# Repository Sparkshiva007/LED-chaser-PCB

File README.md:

# LED Chaser Circuit (555 Timer + CD4017) – KiCad Project

A classic LED chaser circuit designed using **KiCad**, powered by a 555 timer and CD4017 decade counter IC. It lights up a series of LEDs one-by-one in sequence, creating a "running light" or "Knight Rider" effect.

---

## 🎯 What This Project Does

- Generates a continuous sequence of LED flashes (like chasing lights)
- Uses simple and easily available ICs: 555 Timer & CD4017
- Adjustable speed using a timing resistor/capacitor combo
- Designed as a **KiCad project** with proper PCB layout and schematic
- Great for learning KiCad, PCB design, or digital electronics

---

## 📦 Features

- 10 output LEDs (can be reduced as needed)
- 555 Timer in **astable mode** for clock generation
- CD4017 Decade Counter to handle sequencing
- Clean PCB layout with labeled connectors and components
- Optional trimmer resistor to control LED chasing speed

---

## 🧰 Components Used

| Component        | Quantity |
|------------------|----------|
| 555 Timer IC     | 1        |
| CD4017 IC        | 1        |
| LEDs             | 10       |
| 1kΩ Resistors    | 10       |
| 10kΩ potentiometer   | 1        |
| 100nF Capacitor  | 1        |
| 10µF Capacitor   | 1        |
| Power Source (5V–9V) | 1    |

---

## 🚀 How to Use

1. **Open the project** in KiCad 7.x or newer.
2. View/edit the schematic in the `.kicad_sch` file.
3. Open the `.kicad_pcb` file to view or modify the PCB layout.
4. Export Gerber files if you want to fabricate the board.
5. Assemble the board using through-hole components.
6. Power it up and enjoy the chasing LED effect!

## 🔧 Tuning the Speed

You can control how fast the LEDs chase using the **10k potentiometer** connected to the 555 timer. The values used are:

---

## 💡 Educational Value

This is a beginner-friendly project that introduces:
- Basic timer circuits
- Counter IC operation
- Sequential logic
- KiCad schematic and PCB design

Perfect for hobbyists, students, or anyone getting started with PCB design!

---

## Credits

Circuit concept inspired by the classic LED chaser project found in many electronics books. This version was fully re-created in KiCad by **Shiva Projects** for educational use.

---

## 📄 License

Open-source hardware. You are free to modify, improve, or manufacture the board for personal or educational use.

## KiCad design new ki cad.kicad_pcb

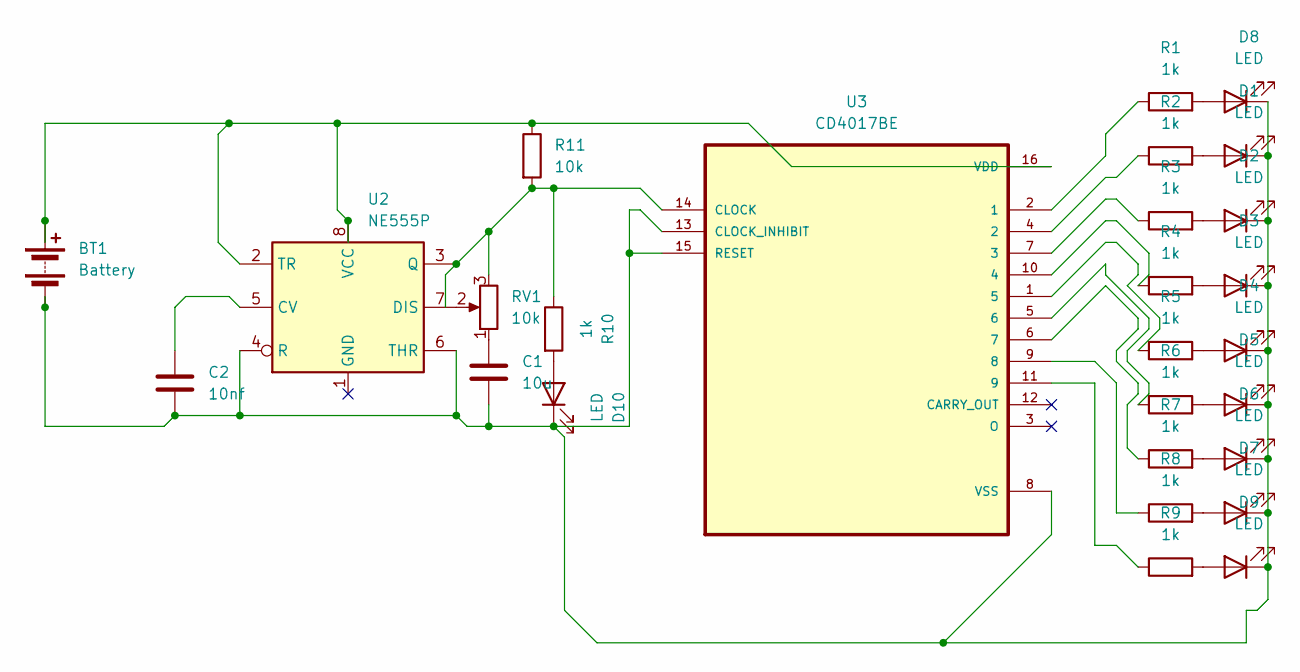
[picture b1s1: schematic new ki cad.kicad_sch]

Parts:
BT1: Battery; BarrelJack_CUI_PJ-063AH_Horizontal
C1: 10u; CP_Radial_D6.3mm_P2.50mm
C2: 10nf; C_Disc_D9.0mm_W5.0mm_P5.00mm
D1, D2, D3, D4, D5, D6, D7, D8, D9, D10: LED; LED_D3.0mm
R1, R3, R4, R5, R6, R7, R8, R9, R10: 1k; R_Axial_DIN0204_L3.6mm_D1.6mm_P7.62mm_Horizontal
R2: 1k; R_Axial_DIN0204_L3.6mm_D1.6mm_P5.08mm_Vertical
R11: 10k; Potentiometer_Bourns_3339P_Vertical
RV1: 10k; R_Axial_DIN0204_L3.6mm_D1.6mm_P7.62mm_Horizontal
U2: NE555P; DIP-8_W7.62mm
U3: CD4017BE; DIP-16_W7.62mm_LongPads

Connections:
unnamed: BT1.1 (+), R11.1, U2.2 (TR), U2.8 (VCC), U3.16 (VDD)
unnamed: BT1.2 (-), C1.2, C2.2, D1.1 (K), D2.1 (K), D3.1 (K), D4.1 (K), D5.1 (K), D6.1 (K), D7.1 (K), D8.1 (K), D9.1 (K), D10.1 (K), U2.4 (R), U2.6 (THR), U3.8 (VSS), U3.13 (CLOCK_INHIBIT), U3.15 (RESET)
unnamed: C1.1, RV1.1
unnamed: D1.2 (A), R2.2
unnamed: D2.2 (A), R3.2
unnamed: D3.2 (A), R4.2
unnamed: D4.2 (A), R5.2
unnamed: D5.2 (A), R6.2
unnamed: D6.2 (A), R7.2
unnamed: D7.2 (A), R8.2
unnamed: D8.2 (A), R1.2
unnamed: D9.2 (A), R9.2
unnamed: D10.2 (A), R10.2
unnamed: C2.1, U2.5 (CV)
unnamed: RV1.2, U2.7 (DIS)
unnamed: R10.1, R11.2, RV1.3, U2.3 (Q), U3.14 (CLOCK)
unnamed: R1.1, U3.2 (1)
unnamed: R2.1, U3.4 (2)
unnamed: R3.1, U3.7 (3)
unnamed: R4.1, U3.10 (4)
unnamed: R5.1, U3.1 (5)
unnamed: R6.1, U3.5 (6)
unnamed: R7.1, U3.6 (7)
unnamed: R8.1, U3.9 (8)
unnamed: R9.1, U3.11 (9)

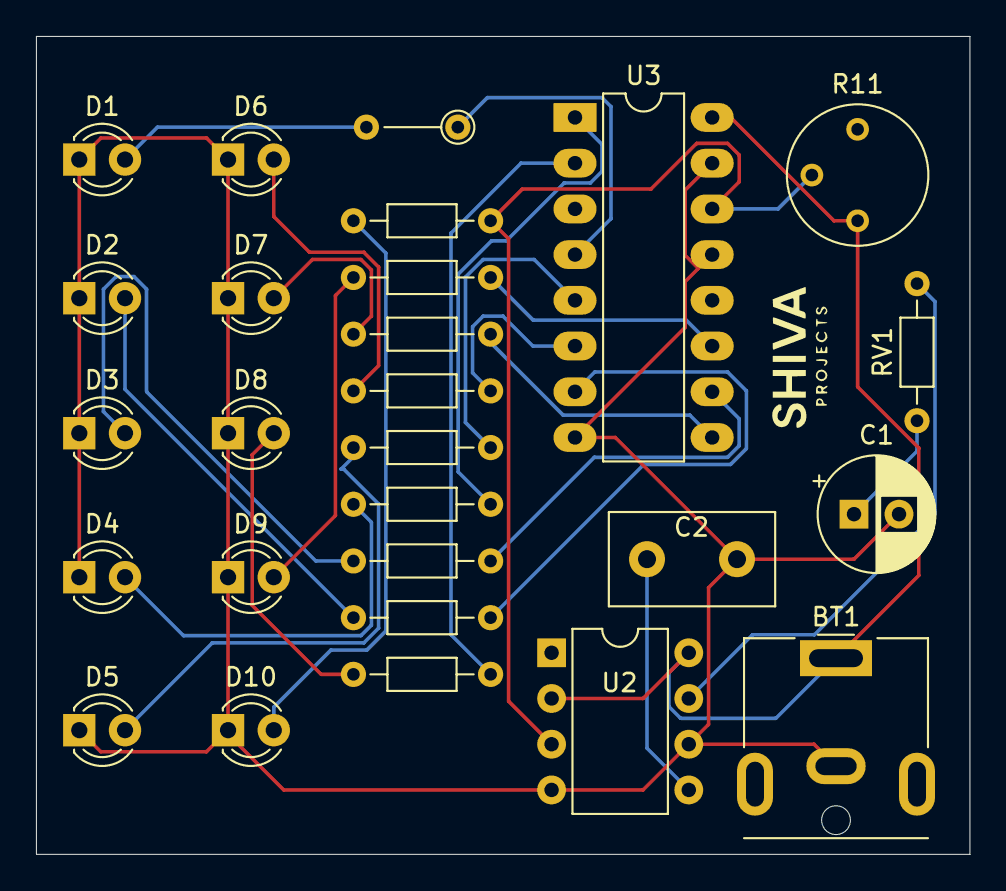
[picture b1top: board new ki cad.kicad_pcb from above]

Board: 2 copper layers, 51.9 x 45.4 mm, 27 parts (0 on the bottom side), 25 nets.
